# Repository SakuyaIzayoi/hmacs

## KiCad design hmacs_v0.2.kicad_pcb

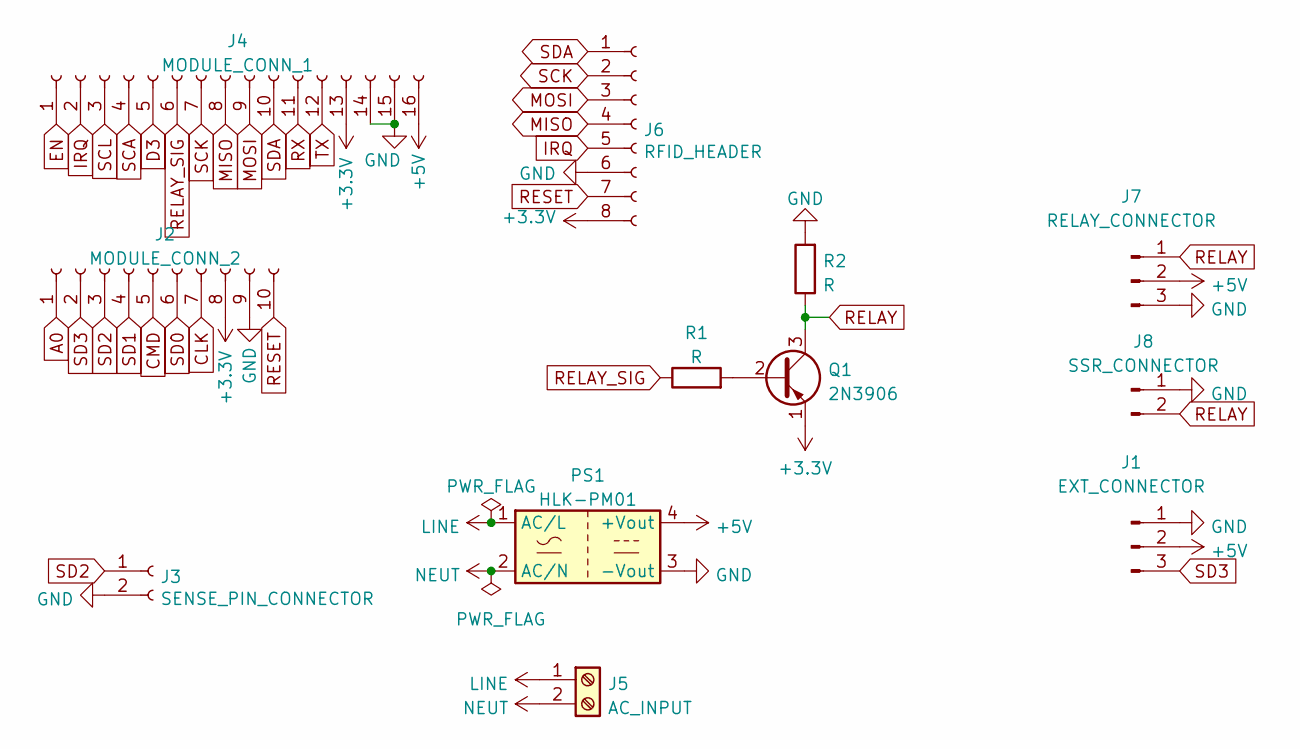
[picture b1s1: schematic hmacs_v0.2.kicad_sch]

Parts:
J1: EXT_CONNECTOR; PinHeader_1x03_P2.54mm_Vertical
J2: MODULE_CONN_2; PinSocket_1x10_P2.54mm_Vertical
J3: SENSE_PIN_CONNECTOR; PinHeader_1x02_P2.54mm_Vertical
J4: MODULE_CONN_1; PinSocket_1x16_P2.54mm_Vertical
J5: AC_INPUT; HANDSON_KF301-2P
J6: RFID_HEADER; PinSocket_1x08_P2.54mm_Vertical
J7: RELAY_CONNECTOR; PinHeader_1x03_P2.54mm_Vertical
J8: SSR_CONNECTOR; PinHeader_1x02_P2.54mm_Vertical
PS1: HLK-PM01; Converter_ACDC_HiLink_HLK-PMxx
Q1: 2N3906; TO-92_Inline
R1, R2: R; R_Axial_DIN0204_L3.6mm_D1.6mm_P7.62mm_Horizontal

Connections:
+3V3: J2.8, J4.13, J6.8, Q1.1 (E)
+5V: J1.2, J4.16, J7.2, PS1.4 (+Vout)
A0: J2.1
CLK: J2.7
CMD: J2.5
D3: J4.5
EN: J4.1
GND: J1.1, J2.9, J3.2, J4.14, J4.15, J6.6, J7.3, J8.1, PS1.3 (-Vout), R2.2
IRQ: J4.2, J6.5
LINE: J5.1, PS1.1 (AC/L)
MISO: J4.8, J6.4
MOSI: J4.9, J6.3
NEUT: J5.2, PS1.2 (AC/N)
unnamed: Q1.2 (B), R1.2
RELAY: J7.1, J8.2, Q1.3 (C), R2.1
RELAY_SIG: J4.6, R1.1
RESET: J2.10, J6.7
RX: J4.11
SCA: J4.4
SCK: J4.7, J6.2
SCL: J4.3
SD0: J2.6
SD1: J2.4
SD2: J2.3, J3.1
SD3: J1.3, J2.2
SDA: J4.10, J6.1
TX: J4.12

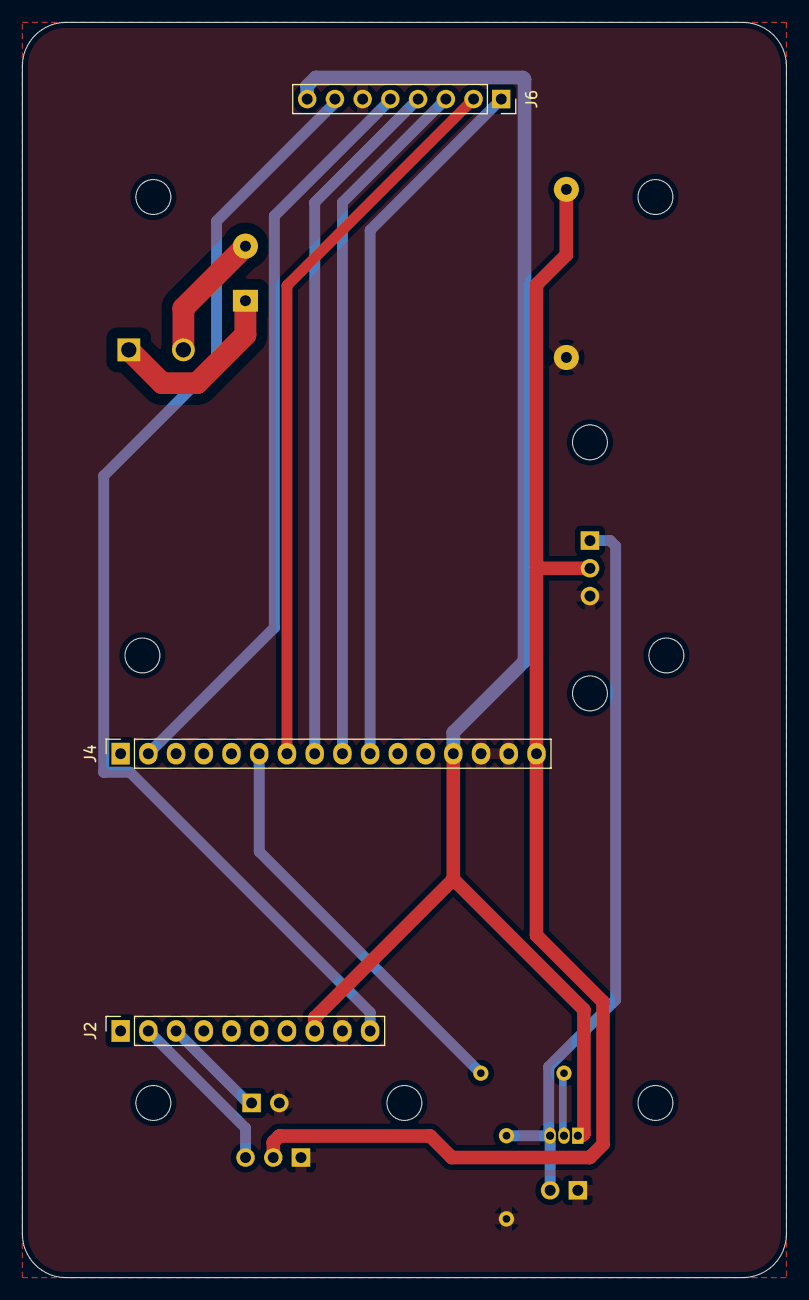
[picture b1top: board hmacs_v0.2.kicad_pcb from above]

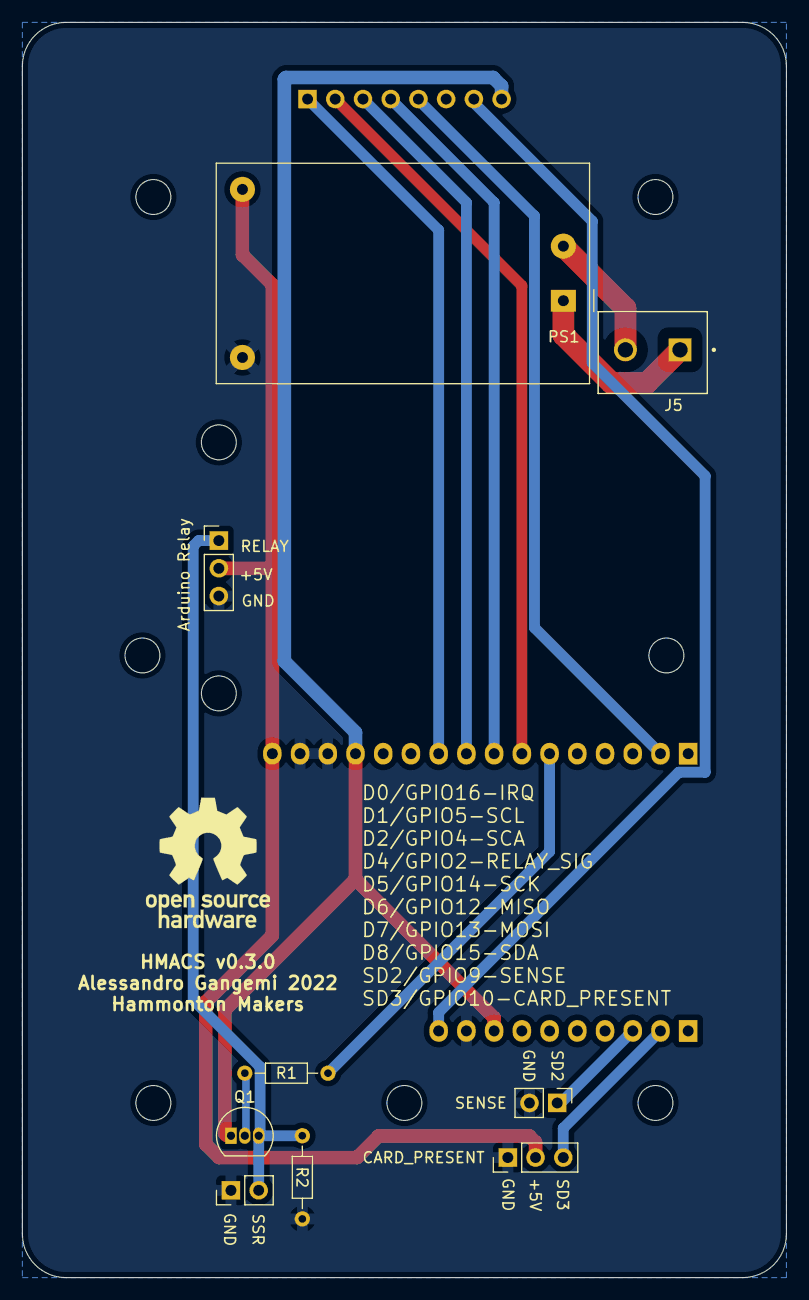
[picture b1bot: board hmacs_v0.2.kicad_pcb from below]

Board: 2 copper layers, 70.0 x 115.0 mm, 12 parts (9 on the bottom side), 16 nets.

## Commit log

2022-04-30 Remove backup files
2022-05-04 Run DRC and push some things around
2022-05-07 Final changes before first manufacturing run
2022-05-07 Add model for screw terminal
2022-06-11 Fix board errors and bump version to 0.3.0
2022-06-11 Remove mounting hole under the AC/DC converter
